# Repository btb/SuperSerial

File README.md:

# SuperSerial

A clone of the Apple Super Serial Card ][

[Interactive BOM](https://btb.github.io/SuperSerial/bom/SuperSerial_rev1.html)

## Assembly

### ROM

UC4 is any 2716 or equivalent PROM/EPROM/EEPROM, programmed with the [SSC firmware](https://mirrors.apple2.org.za/Apple%20II%20Documentation%20Project/Interface%20Cards/Serial/Apple%20II%20Super%20Serial%20Card/ROM%20Images/). You can also use a larger/more modern chip such as a 28C256, but note that A11 and A13 will be permanently tied high, and A12 and A14 will be permanently tied low. This means the 2K of firmware code must sit at the 2800h region in the PROM (you can just do what I usually do and fill the entire ROM with repeated copies).

### ACIA

UA4 should be a new old stock MOS 6551 or equivalent. The WDC 65C51 has a well-known bug that likely makes it unsuitable for some uses, though it may be fine for others.

### Oscillator

The original SSC used a 1.8432MHz crystal (Y1) and a usually-omitted 10pF capacitor (C1) for timing the ACIA chip. You can use this same kind of crystal, or you can use a self-contained DIP8 or DIP14 oscillator (G1). If you use a horizontally-mounted crystal at Y1, make sure it is insulated from the unused pads underneath.

Crystal option: 

### Cable Header

You can use a common PC-type IDC10 to DB9M pigtail, or the IDC10 to DB25F pigtail used with the original Apple SSC. There are two different pinouts used in the PC style ("sequential" or "staggered"), and the "apple" pinout is different from both. Only populate the header (J1) for the style you're going to use. "sequential" is the most commonly available type. A keyed/shrouded header is probably best, a right angle/horizontal header would be nice, but you probably only have room for that if you are using the "apple" pinout.

Sequential: 
Staggered: 

### Driver/Receiver

The RS232 Driver/Receiver chips, UA6 and UA7, can be the original MC1488 and MC1489 or equivalents like the 75188 and 75189, or the CMOS equivalents 14C88 and 14C89. If UA6 is a 14C88, you can omit capacitors C3, C4, and C9.

## Configuration

### Modem/Terminal mode

The original SSC used a large DIP16 sized jumper block that could be oriented in two ways for "terminal" or "modem" modes. This card is simply in permanent "modem" mode. If "terminal" mode is required, use a null-modem cable or adapter.

### Configuration jumpers

The original SSC had two sets of 7-position dip switches, for a wide variety of default software settings, this card has no switches, just two sets of 6-position solder jumpers on the rear of the card. These are pre-configured to the use the reasonable modem defaults of:

    SW1: 100111  SW2: 110110

You can cut these traces and re-solder as needed. Note that all of these settings (except for SW2-6) are configurable from software as well. But if you commonly need to use the card for more than one purpose, it's probably best to just have more than one card!

SW1-7 and SW2-7 are omitted since those do not control software defaults, but re-route some signals to non-standard pins. If that's necessary for you, you can use an adapter cable.

## Mounting

Want to make a OEM-style metal bracket to mount your connector to the rear of your Apple II or II+? See my design here: https://github.com/btb/Apple2IOClamps

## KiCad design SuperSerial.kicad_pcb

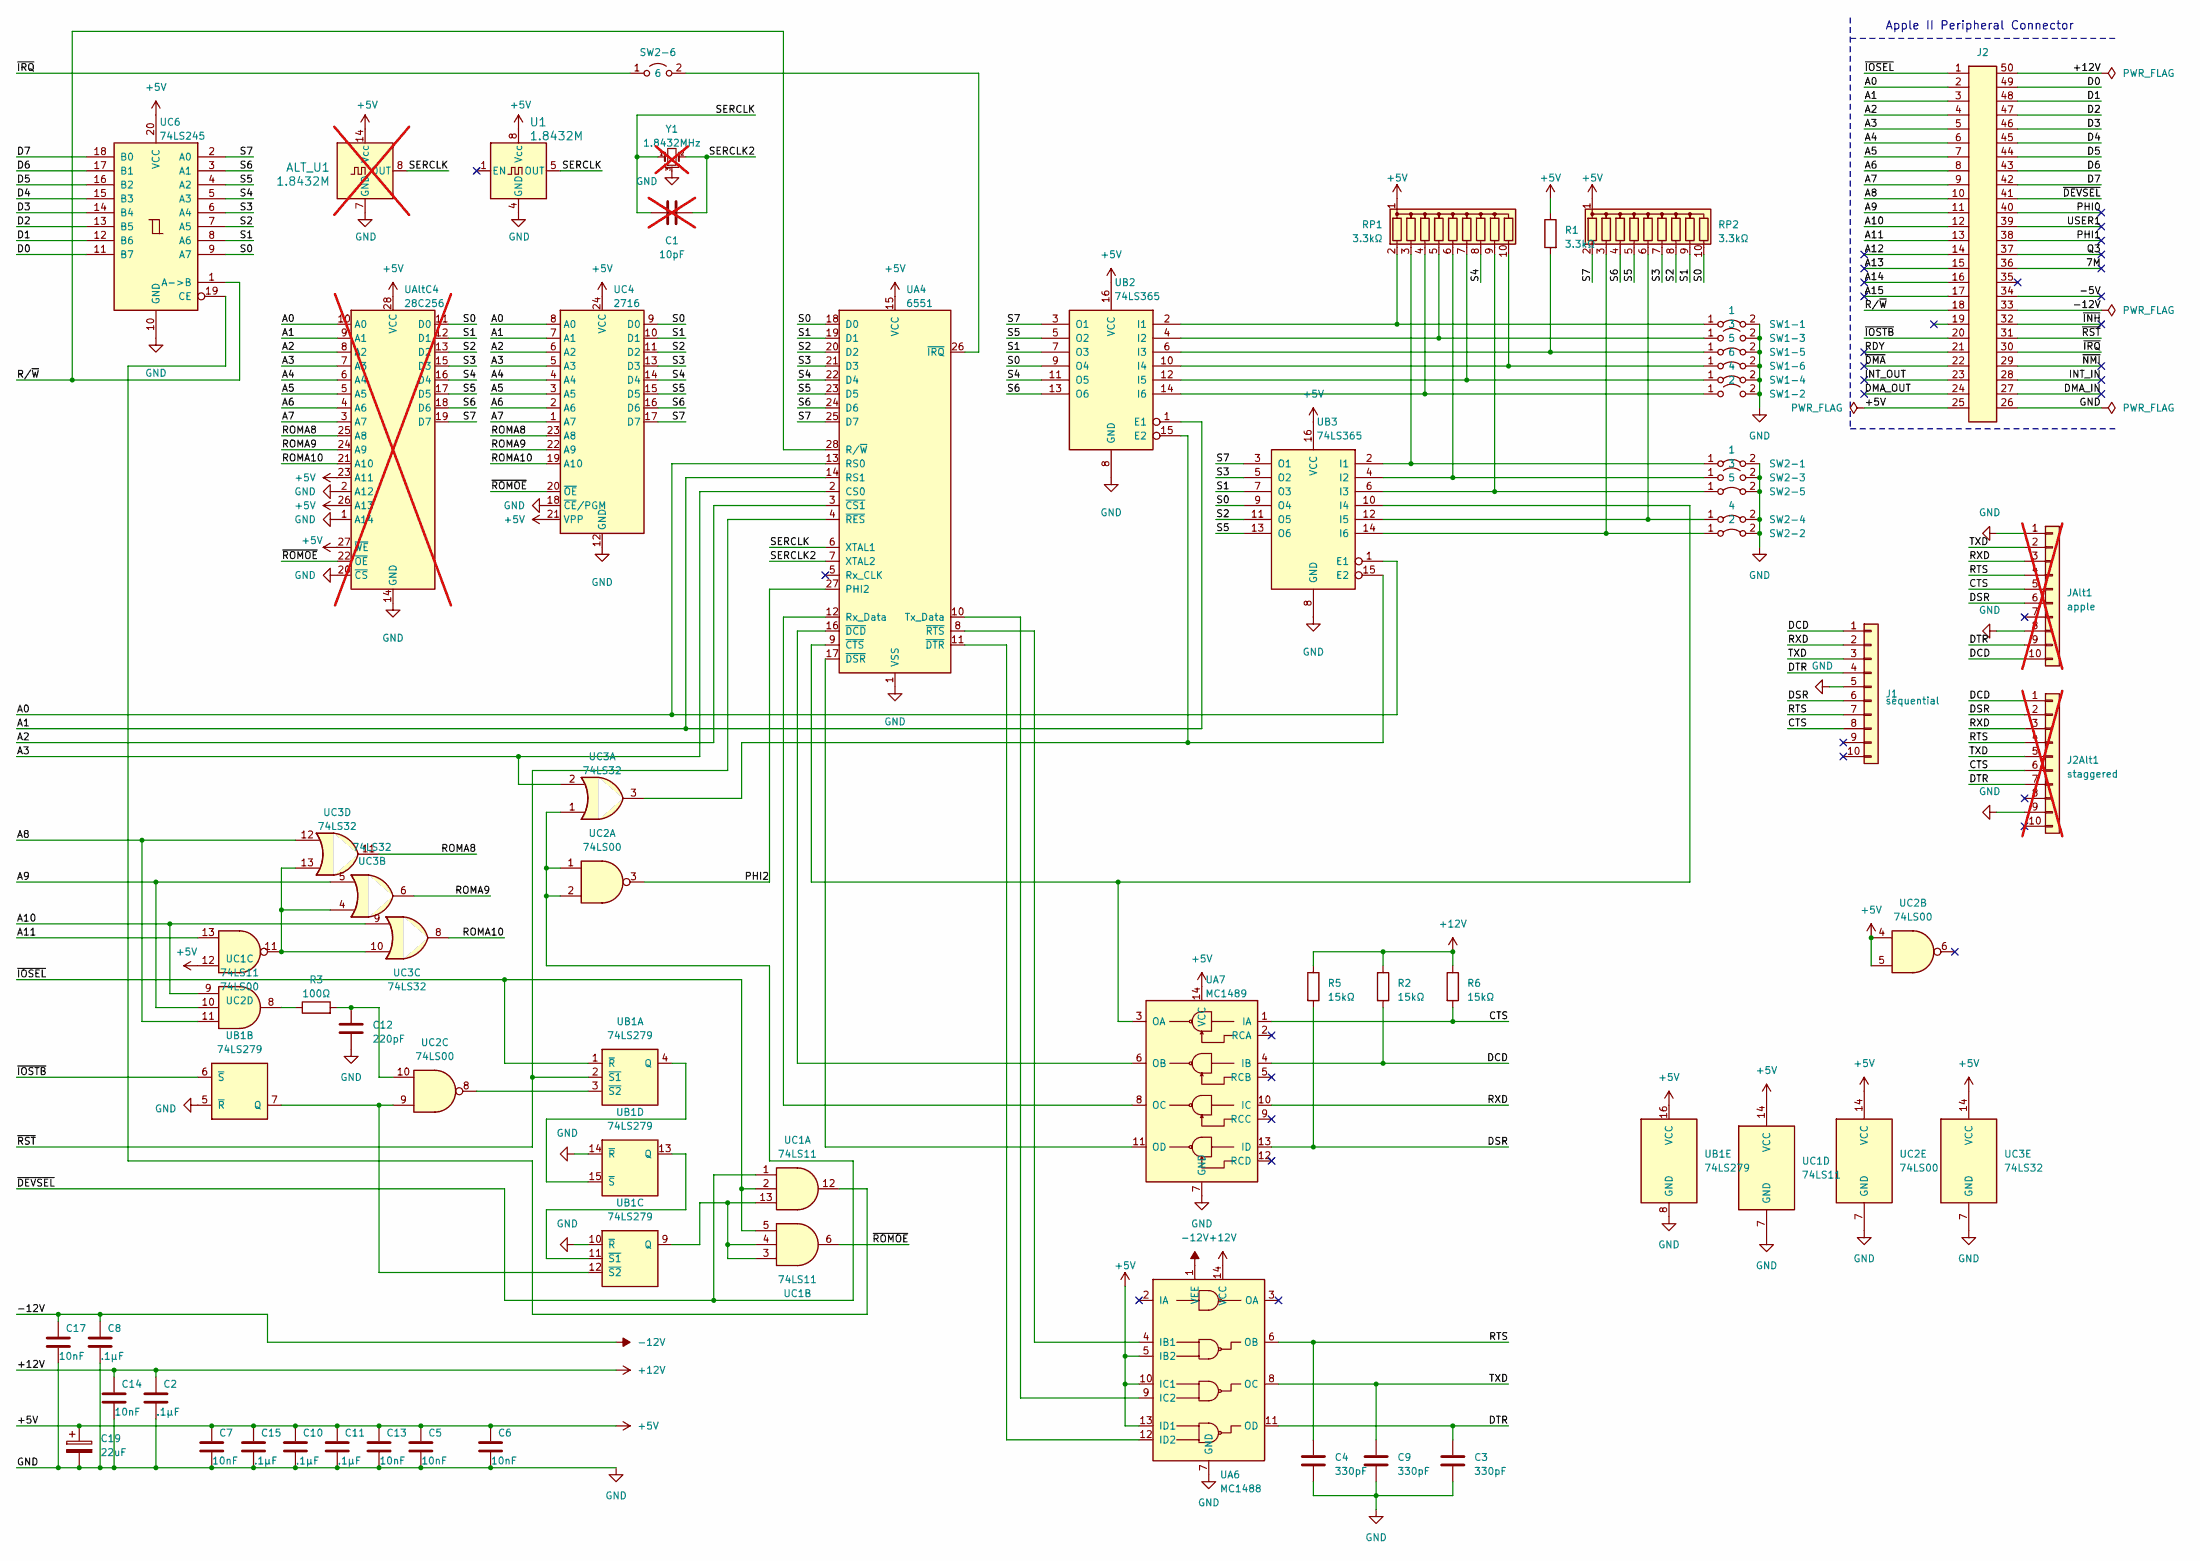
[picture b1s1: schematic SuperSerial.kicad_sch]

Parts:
ALT_U1: 1.8432M; Oscillator_DIP-14; not fitted
C1: 10pF; C_Disc_D3.0mm_W1.6mm_P2.50mm; not fitted
C2, C8, C10, C11, C15: .1µF; C_Disc_D4.3mm_W1.9mm_P5.00mm
C3, C4, C9: 330pF; C_Disc_D3.0mm_W1.6mm_P2.50mm
C5, C6, C7, C13, C14, C17: 10nF; C_Disc_D4.3mm_W1.9mm_P5.00mm
C12: 220pF; C_Disc_D4.3mm_W1.9mm_P5.00mm
C19: 22uF; CP_Radial_D5.0mm_P2.50mm
J1: sequential; PinHeader_2x5_P2.54mm_Vertical_Shrouded
J2: Apple II Expansion Bus; Apple II Expansion Edge Connector
J2Alt1: staggered; PinHeader_2x5_P2.54mm_Vertical_Shrouded; not fitted
JAlt1: apple; PinHeader_2x5_P2.54mm_Vertical_Shrouded; not fitted
R1: 3.3kΩ; R_Axial_DIN0207_L6.3mm_D2.5mm_P10.16mm_Horizontal
R2, R5, R6: 15kΩ; R_Axial_DIN0207_L6.3mm_D2.5mm_P10.16mm_Horizontal
R3: 100Ω; R_Axial_DIN0207_L6.3mm_D2.5mm_P10.16mm_Horizontal
RP1, RP2: 3.3kΩ; R_Array_SIP10
SW1-1, SW2-1: 1; SolderJumper-2_P1.3mm_Bridged_RoundedPad1.0x1.5mm
SW1-2: 2; SolderJumper-2_P1.3mm_Open_RoundedPad1.0x1.5mm
SW1-3, SW2-3: 3; SolderJumper-2_P1.3mm_Open_RoundedPad1.0x1.5mm
SW1-4, SW2-4: 4; SolderJumper-2_P1.3mm_Bridged_RoundedPad1.0x1.5mm
SW1-5, SW2-5: 5; SolderJumper-2_P1.3mm_Bridged_RoundedPad1.0x1.5mm
SW1-6: 6; SolderJumper-2_P1.3mm_Bridged_RoundedPad1.0x1.5mm
SW2-2: 2; SolderJumper-2_P1.3mm_Bridged_RoundedPad1.0x1.5mm
SW2-6: 6; SolderJumper-2_P1.3mm_Open_RoundedPad1.0x1.5mm
U1: 1.8432M; Oscillator_DIP-8
UA4: 6551; DIP-28_W15.24mm
UA6: MC1488; DIP-14_W7.62mm
UA7: MC1489; DIP-14_W7.62mm
UAltC4: 28C256; DIP-28_W15.24mm; not fitted
UB1: 74LS279; DIP-16_W7.62mm
UB2, UB3: 74LS365; DIP-16_W7.62mm
UC1: 74LS11; DIP-14_W7.62mm
UC2: 74LS00; DIP-14_W7.62mm
UC3: 74LS32; DIP-14_W7.62mm
UC4: 2716; DIP-24_W15.24mm
UC6: 74LS245; DIP-20_W7.62mm
Y1: 1.8432MHz; Crystal_HC49-U_Horizontal_1EP_style2; not fitted

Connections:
+5V: C5.1, C6.1, C7.1, C10.1, C11.1, C13.1, C15.1, C19.1, J2.25 (+5V), R1.1, RP1.1 (common), RP2.1 (common), UA4.15 (VCC), UA6.5 (IB2), UA6.10 (IC1), UA6.13 (ID1), UA7.14 (VCC), UAltC4.23 (A11), UAltC4.26 (A13), UAltC4.27 (~WE), UAltC4.28 (VCC), UB1.16 (VCC), UB2.16 (VCC), UB3.16 (VCC), UC1.14 (VCC), UC2.4, UC2.5, UC2.12, UC2.14 (VCC), UC3.14 (VCC), UC4.21 (VPP), UC4.24 (VCC), UC6.20 (VCC); also elsewhere on the board
+12V: C2.1, C14.1, J2.50 (-12V), R2.1, R5.1, R6.1, UA6.14 (VCC)
-12V: C8.1, C17.1, J2.33 (-12V), UA6.1 (VEE)
/7M: J2.36 (7M)
/-5V: J2.34 (-5V)
/A0: J2.2 (A00), UA4.13 (RS0), UAltC4.10 (A0), UB3.1 (E1), UC4.8 (A0)
/A1: J2.3 (A01), UA4.14 (RS1), UAltC4.9 (A1), UB2.1 (E1), UC4.7 (A1)
/A2: J2.4 (A02), UA4.3 (~CS1), UAltC4.8 (A2), UC4.6 (A2)
/A3: J2.5 (A03), UA4.2 (CS0), UAltC4.7 (A3), UC3.2, UC4.5 (A3)
/A4: J2.6 (A04), UAltC4.6 (A4), UC4.4 (A4)
/A5: J2.7 (A05), UAltC4.5 (A5), UC4.3 (A5)
/A6: J2.8 (A06), UAltC4.4 (A6), UC4.2 (A6)
/A7: J2.9 (A07), UAltC4.3 (A7), UC4.1 (A7)
/A8: J2.10 (A08), UC1.11, UC3.12
/A9: J2.11 (A09), UC1.10, UC3.5
/A10: J2.12 (A10), UC1.9, UC3.9
/A11: J2.13 (A11), UC2.13
/A12: J2.14 (A12)
/A13: J2.15 (A13)
/A14: J2.16 (A14)
/A15: J2.17 (A15)
/CTS: J1.8, J2Alt1.6, JAlt1.5, R6.2, UA7.1 (IA)
/D0: J2.49 (D0), UC6.11 (B7)
/D1: J2.48 (D1), UC6.12 (B6)
/D2: J2.47 (D2), UC6.13 (B5)
/D3: J2.46 (D3), UC6.14 (B4)
/D4: J2.45 (D4), UC6.15 (B3)
/D5: J2.44 (D5), UC6.16 (B2)
/D6: J2.43 (D6), UC6.17 (B1)
/D7: J2.42 (D7), UC6.18 (B0)
/DCD: J1.1, J2Alt1.1, JAlt1.10, R2.2, UA7.4 (IB)
/DMA_IN: J2.27 (DMA_IN)
/DMA_OUT: J2.24 (DMA_OUT)
/DSR: J1.6, J2Alt1.2, JAlt1.6, R5.2, UA7.13 (ID)
/DTR: C3.1, J1.4, J2Alt1.7, JAlt1.9, UA6.11 (OD)
/INT_IN: J2.28 (INT_IN)
/INT_OUT: J2.23 (INT_OUT)
/PHI0: J2.40 (PHI0)
/PHI1: J2.38 (PHI1)
/PHI2: UA4.27 (PHI2), UC2.3
/Q3: J2.37 (Q3)
/RDY: J2.21 (RDY)
/ROMA8: UAltC4.25 (A8), UC3.11, UC4.23 (A8)
/ROMA9: UAltC4.24 (A9), UC3.6, UC4.22 (A9)
/ROMA10: UAltC4.21 (A10), UC3.8, UC4.19 (A10)
/RTS: C4.1, J1.7, J2Alt1.4, JAlt1.4, UA6.6 (OB)
/RXD: J1.2, J2Alt1.3, JAlt1.3, UA7.10 (IC)
/R/~W: J2.18 (R/~W), UA4.28 (R/~W), UC6.1 (A->B)
/S0: RP2.10 (R9), UA4.18 (D0), UAltC4.11 (D0), UB2.9 (O4), UB3.9 (O4), UC4.9 (D0), UC6.9 (A7)
/S1: RP2.9 (R8), UA4.19 (D1), UAltC4.12 (D1), UB2.7 (O3), UB3.7 (O3), UC4.10 (D1), UC6.8 (A6)
/S2: RP2.8 (R7), UA4.20 (D2), UAltC4.13 (D2), UB3.11 (O5), UC4.11 (D2), UC6.7 (A5)
/S3: RP2.7 (R6), UA4.21 (D3), UAltC4.15 (D3), UB3.5 (O2), UC4.13 (D3), UC6.6 (A4)
/S4: RP1.8 (R7), UA4.22 (D4), UAltC4.16 (D4), UB2.11 (O5), UC4.14 (D4), UC6.5 (A3)
/S5: RP2.5 (R4), UA4.23 (D5), UAltC4.17 (D5), UB2.5 (O2), UB3.13 (O6), UC4.15 (D5), UC6.4 (A2)
/S6: RP2.4 (R3), UA4.24 (D6), UAltC4.18 (D6), UB2.13 (O6), UC4.16 (D6), UC6.3 (A1)
/S7: RP2.2 (R1), UA4.25 (D7), UAltC4.19 (D7), UB2.3 (O1), UB3.3 (O1), UC4.17 (D7), UC6.2 (A0)
/SERCLK: C1.1, UA4.6 (XTAL1), Y1.1; also elsewhere on the board
/SERCLK2: C1.2, UA4.7 (XTAL2), Y1.2
/TXD: C9.1, J1.3, J2Alt1.5, JAlt1.2, UA6.8 (OC)
/USER1: J2.39 (USER1)
/~DEVSEL: J2.41 (~DEVICE_SELECT), UC1.1, UC2.1, UC2.2, UC3.1
/~DMA: J2.22 (~DMA)
/~INH: J2.32 (~INH)
/~IOSEL: J2.1 (~IO_SELECT), UB1.1 (~R), UC1.2, UC1.5
/~IOSTB: J2.20 (~I/O_STROBE), UB1.6 (~S)
/~IRQ: J2.30 (~IRQ), SW2-6.1 (A)
/~NMI: J2.29 (~NMI)
/~ROMOE: UAltC4.22 (~OE), UC1.6, UC4.20 (~OE)
/~RST: J2.31 (~RES), UA4.4 (~RES), UB1.2 (~S1)
GND: C2.2, C3.2, C4.2, C5.2, C6.2, C7.2, C8.2, C9.2, C10.2, C11.2, C12.2, C13.2, C14.2, C15.2, C17.2, C19.2, J1.5, J2.26 (GND), J2Alt1.9, JAlt1.1, JAlt1.8, SW1-1.2 (B), SW1-2.2 (B), SW1-3.2 (B), SW1-4.2 (B), SW1-5.2 (B), SW1-6.2 (B), SW2-1.2 (B), SW2-2.2 (B), SW2-3.2 (B), SW2-4.2 (B), SW2-5.2 (B), UA4.1 (VSS), UA6.7 (GND), UA7.7 (GND), UAltC4.1 (A14), UAltC4.2 (A12), UAltC4.14 (GND), UAltC4.20 (~CS), UB1.5 (~R), UB1.8 (GND), UB1.10 (~R), UB1.14 (~R), UB2.8 (GND), UB3.8 (GND), UC1.7 (GND), UC2.7 (GND), UC3.7 (GND), UC4.12 (GND), UC4.18 (~CE/PGM), UC6.10 (GND), Y1.3; also elsewhere on the board
unnamed: C12.1, R3.2, UC2.10
unnamed: R3.1, UC1.8
unnamed: RP1.2 (R1), SW1-1.1 (A), UB2.2 (I1)
unnamed: RP1.3 (R2), SW2-1.1 (A), UB3.2 (I1)
unnamed: RP1.4 (R3), SW1-2.1 (A), UB2.14 (I6)
unnamed: RP1.5 (R4), SW1-3.1 (A), UB2.4 (I2)
unnamed: RP1.6 (R5), SW2-3.1 (A), UB3.4 (I2)
unnamed: RP1.7 (R6), SW1-4.1 (A), UB2.12 (I5)
unnamed: RP1.9 (R8), SW2-5.1 (A), UB3.6 (I3)
unnamed: RP1.10 (R9), SW1-6.1 (A), UB2.10 (I4)
unnamed: RP2.3 (R2), SW2-2.1 (A), UB3.14 (I6)
unnamed: RP2.6 (R5), SW2-4.1 (A), UB3.12 (I5)
unnamed: R1.2, SW1-5.1 (A), UB2.6 (I3)
unnamed: SW2-6.2 (B), UA4.26 (~IRQ)
unnamed: UA4.12 (Rx_Data), UA7.8 (OC)
unnamed: UA4.10 (Tx_Data), UA6.9 (IC2)
unnamed: UA4.9 (~CTS), UA7.3 (OA), UB3.10 (I4)
unnamed: UA4.16 (~DCD), UA7.6 (OB)
unnamed: UA4.17 (~DSR), UA7.11 (OD)
unnamed: UA4.11 (~DTR), UA6.12 (ID2)
unnamed: UA4.8 (~RTS), UA6.4 (IB1)
unnamed: UB1.4 (Q), UB1.15 (~S)
unnamed: UB1.3 (~S2), UC2.8
unnamed: UB1.7 (Q), UB1.12 (~S2), UC2.9
unnamed: UB1.9 (Q), UC1.3, UC1.4, UC1.13
unnamed: UB1.11 (~S1), UB1.13 (Q)
unnamed: UB2.15 (E2), UB3.15 (E2), UC3.3
unnamed: UC2.11, UC3.4, UC3.10, UC3.13
unnamed: UC1.12, UC6.19 (CE)

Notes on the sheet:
Apple II Peripheral Connector

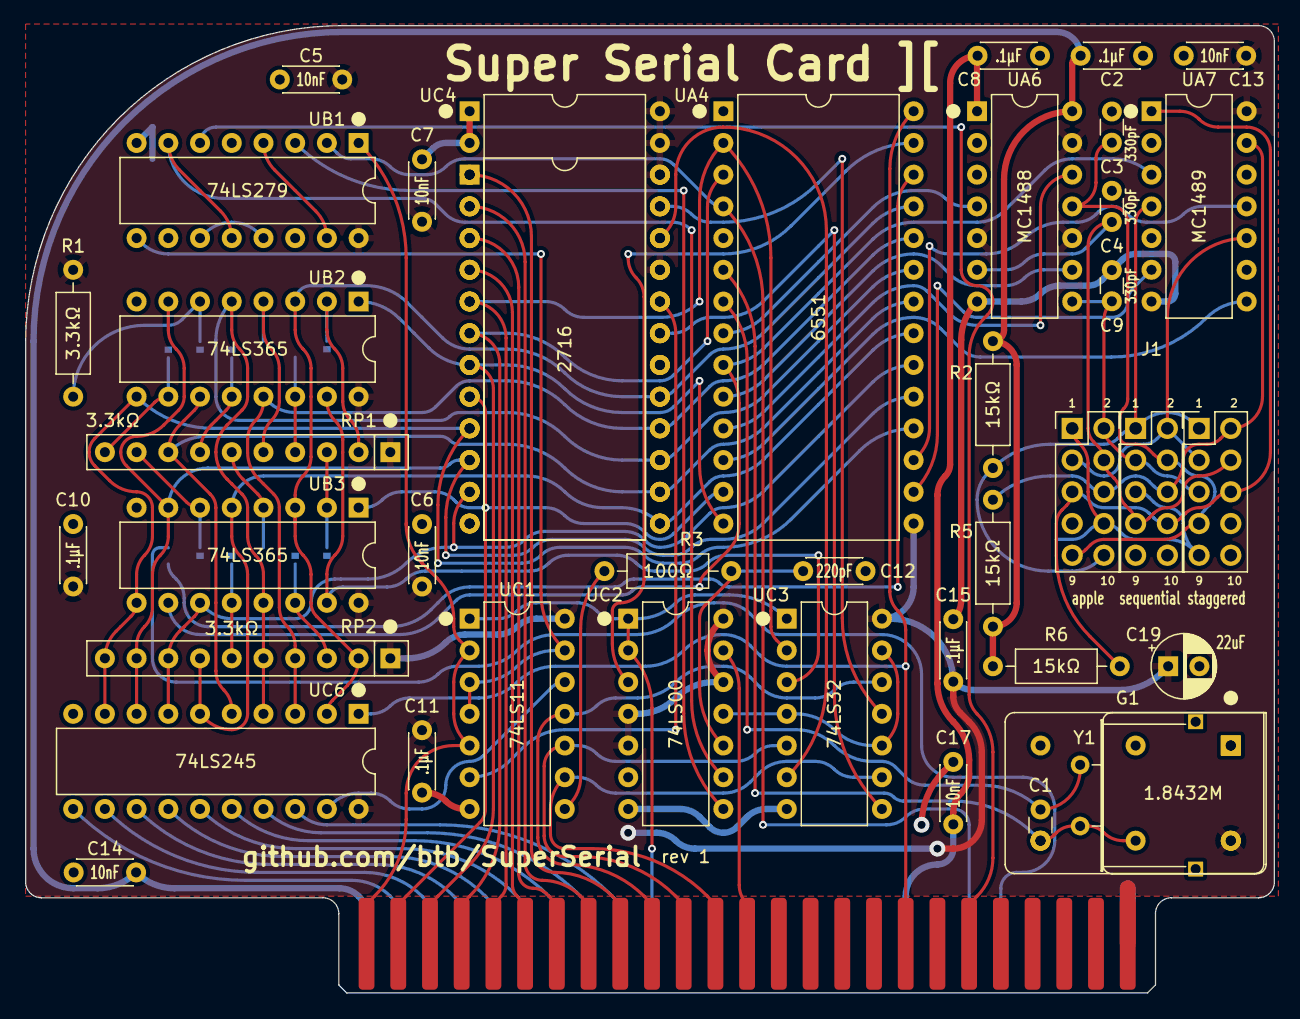
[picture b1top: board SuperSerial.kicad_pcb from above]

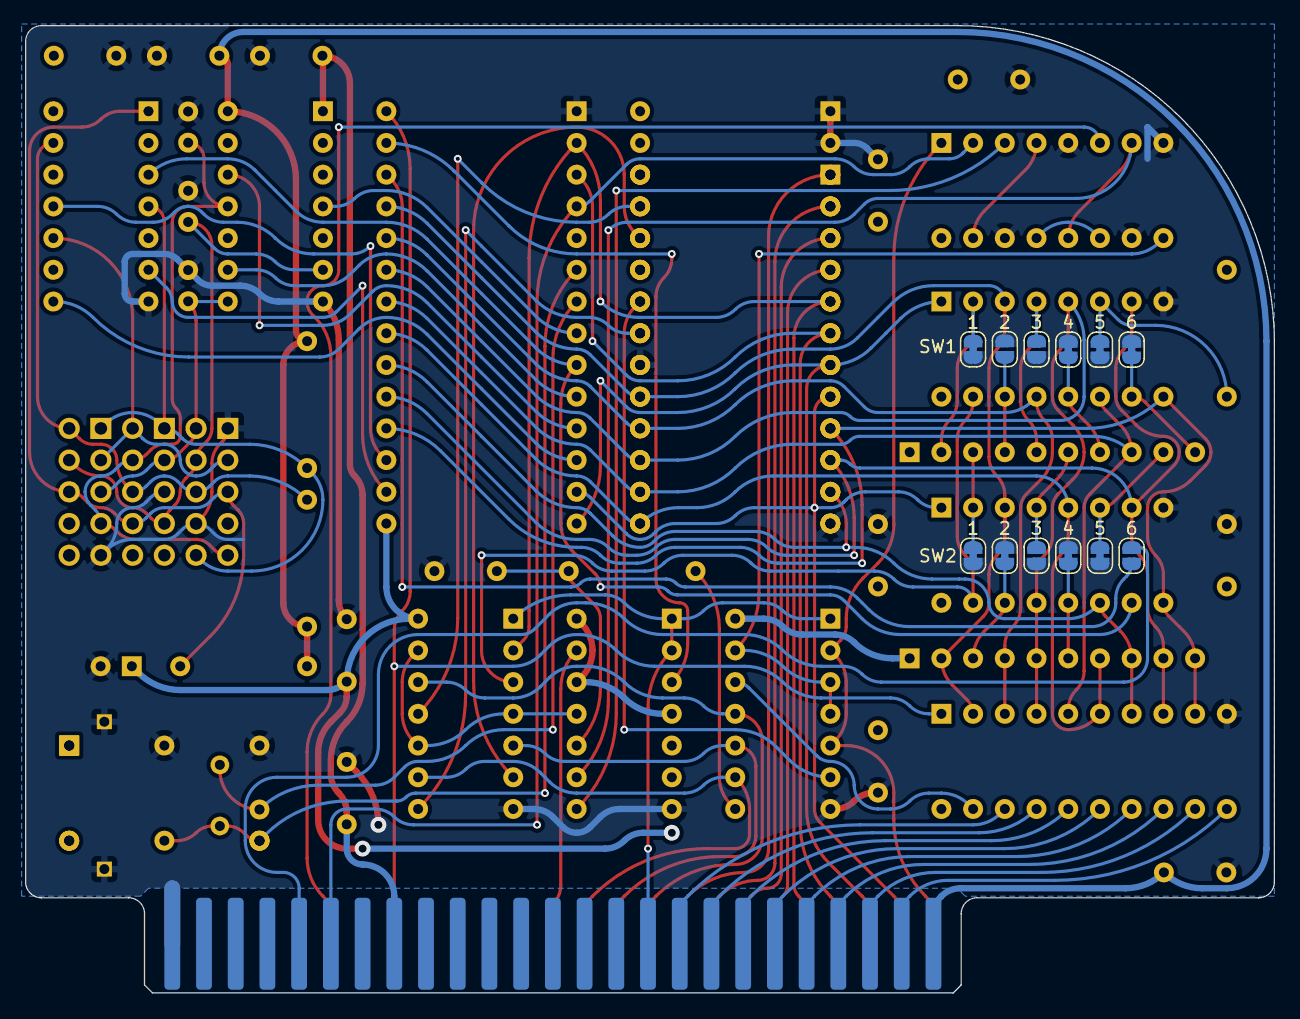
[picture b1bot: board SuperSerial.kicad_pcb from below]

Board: 2 copper layers, 100.0 x 77.5 mm, 55 parts (12 on the bottom side), 81 nets.

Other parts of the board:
G1: 1.8432M; Oscillator_DIP-8
GAlt1: 1.8432M; Oscillator_DIP-14

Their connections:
+5V: G1.8 (Vcc), GAlt1.14 (Vcc); also elsewhere on the board
/SERCLK: G1.5 (OUT), GAlt1.8 (OUT); also elsewhere on the board
GND: G1.4 (GND), GAlt1.7 (GND); also elsewhere on the board

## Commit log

2024-01-23 rev0
2024-01-28 cleanup
2025-03-11 tweak fab text
2025-03-11 fab note C3,C4,C9 optional
2025-03-11 add jumpers image
2025-03-11 show fab layer by default
2025-03-12 Add images for the two PC cable types
2025-03-12 Cleanup, more images
2025-03-12 Update README.md
    note 75188 and 75189
2025-03-12 Update README.md
    Link to brackets
2025-03-12 Move DCD to apple connector pin 10
    Fixes #1
2025-03-12 Bump to rev1
2025-03-12 rev1 images
2025-03-13 restore correct rev0 bom
